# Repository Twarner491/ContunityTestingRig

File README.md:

### Devoloped by [Drew Griggs](http://fabacademy.org/2021/labs/charlotte/students/drew-griggs/about/) and [Teddy Warner](https://teddywarner.org/About-Me/about/).

## Documentation -

Our project idea, as discussed with RhythmLink, is a continuity testing rig. This project will be capable of testing and displaying the results of the pinout connections between two ends of a cable with different headers. Our goal is to create a continuity testing rig capable of testing and displaying the connections between the ends of two different cable headers. We will display the results to a webpage using the Raspberry Pico W microcontroller.

The concept behind this project is simple, but our method of display, as well as some methods to reduce the GPIO pins required for the microcontroller will be quite complex, so we worry that we might run into some issues here. The most challenging part of this project will likely be getting the web server to run correctly, as we will be using a RPI Pico W to host the server, but there are very few examples of a project such as this compared to something like an Arduino. A successful project would be able to test the continuity in real time and refresh the users web browser through a visually appealing display.

We used a few sources as guides to setting up a RPI web server, mainly Tom’s Hardware and the Raspberry Pi website - see the *sources* section below.

Our project is significantly more complex than these simple web servers, however, as we will refresh the page automatically, include some javascript and more complex HTML elements to improve the aesthetic, not to mention the continuity testing aspects.

Through the development of the project, we learned a great deal about the principles of static site design, multimedia design with 3D printing, and the integration of software and hardware components. As we developed the initial design stages of the project, we reminded ourselves of the horrors of debugging, going through countless coexisting issues that were causing the failure of our project. As we built up our initial prototype, we discovered, and ultimately resolved, issues involving our diode array, web server generation, board design, and many more. Similarly to our Fab Academy projects, we had many parts working in conjunction with each other. As we traversed the design and manufacturing process, we once again were reminded of the difficulty of getting each component of the project successfully integrated. At times, we would wonder from which component of the project our errors arose from.

Some of the major issues we encountered were due to errors in the board design. Due to an oversight in the main board, we did not include diodes for the final point of connection between each diode chain and output pin, which caused issues with reading pins that should not be high. Furthermore, we had an issue with our self test function. We initially decided to implement transistors to toggle and check each output and input pin, but due to voltage jumping between Gate and Drain despite no Source voltage, this part was unsuccessful. As such, we will not be making any further changes to the prototype, other than implementing a basic self test function with a predetermined cable.

### Electronic Design

The testing rig will likely consist of two separate boards, one main logic and interpretation board and one header board. The logic board will include a RPi Pico W to host the server and interpret data, a power regulation module, a diode array to reduce specific pins into their binary values (to conserve GPIO pins), and a large 2x20 pin header. The header board will include the connectors for each end of the cable and the 2x20 pin connector, as well as a possible self test function to ensure the functionality of the rig. The self test will include a jump between specific pins on each module, and an LED that will flash green assuming the test passes.

We used a few methods to allow the project to be operable on the Raspberry Pico. We designed and implemented an array of diodes to convert any individual input into a binary representation of its pin value, allowing us to test and read 15 possible different wires through 4 input pins. For the header connector board, we designed custom eagle footprints and libraries for the two types of connectors, as well as adding self-test circuits that will connect pins through the switch of a transistor.

Our project went somewhat to plan. Due to some issues in the testing of our board due to the precision of our lab’s PCB mills as well as the complexity of our board, we had some issues testing the main board. We eventually fixed a bug in the diode array, and the main board was working. The header board took less time, as it was less complex, but due to some issues with voltages jumping across transistors despite no source voltage, we were unable to include our initially planned self test function. After discussions with Rhythmlink, however, we determined that this would not be an issue, and since the board worked without the transistors soldered, we continued with testing. Web and software design and testing took the majority of our allocated time, as this was the first project of this type for both of us, so it took some getting used to programming a web server through micropython.

We mostly used tools oriented to PCB design in our project. We spent the majority of our machine use on the Bantam PCB mills, with some 3D printing of our enclosure towards the end of our project. Our files were EagleCad .sch and .brd schematic and boards, python files, fusion project files, and html files.

### Software

The operation of the Pico makes designing and editing a webpage in real time very annoying. It requires a string object to be sent through a library in the Pico, so we had to code a way to implement the updates of the test through splicing strings together. Apart from some hiccups in the testing of this component, however, the code was fairly simple. It loops through each of nine output pins, and reads the corresponding binary value of the input pins that corresponds to the pin number in the header cable.

### CAD

### Testing

https://github.com/user-attachments/assets/56f717f2-6f56-4a5b-b8bf-3c429beb7c11

https://github.com/user-attachments/assets/bd0a2b19-7a08-46a7-8804-3f2991451b49

### Assembly Instructions

- Download necessary files from github (link above)
- 3D print outer case
- Order or manufacture main and header board
- Solder components to each board
- Download Thonny and the python script
- Use dupont connectors and solid wires to create header cable adapters
- Add your wifi information to the ssid and password in the python file
- Boot the pico w with the boot file. Instructions can be found on raspberry pico article
- Run the script

## Sources -
 - [https://www.tomshardware.com/how-to/raspberry-pi-pico-setup](https://www.tomshardware.com/how-to/raspberry-pi-pico-setup)
 - [https://datasheets.raspberrypi.com/picow/pico-w-datasheet.pdf](https://datasheets.raspberrypi.com/picow/pico-w-datasheet.pdf)

---
- [Fork this repository](https://github.com/Twarner491/ContunityTestingRig/fork)
- [Watch this repo](https://github.com/Twarner491/ContunityTestingRig/subscription)
- [Create issue](https://github.com/Twarner491/ContunityTestingRig/issues/new)

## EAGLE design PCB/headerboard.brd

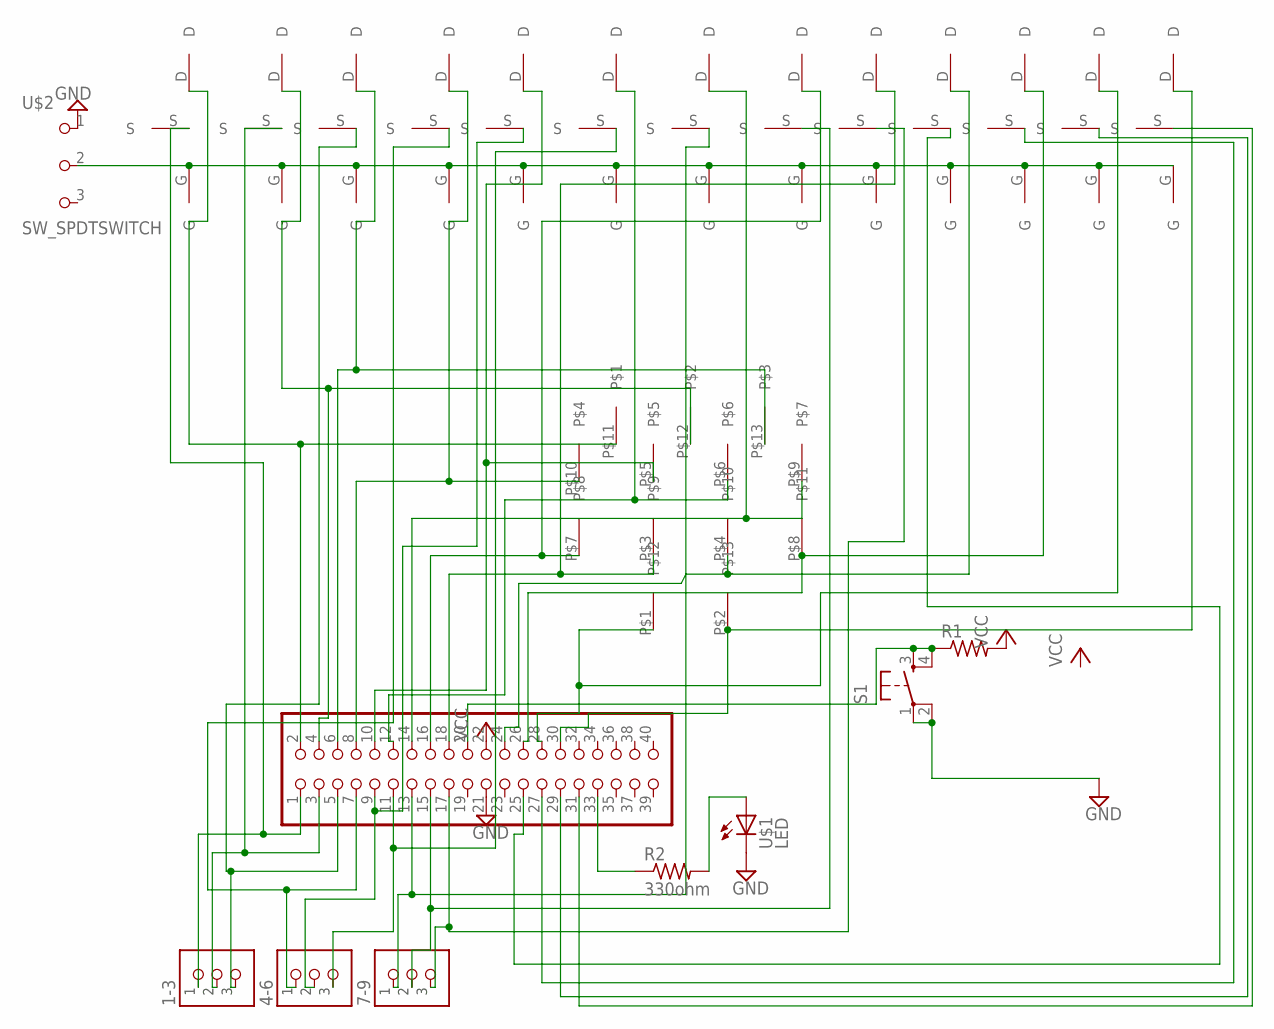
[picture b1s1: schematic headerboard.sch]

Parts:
1-3, 4-6, 7-9: CONN_03_TERM'-FABLAB'; ED555DS-3DS
JP1: PINHD-2X20; 2X20
R1: R1206FAB
R2: 330ohm; R1206FAB
S1: SW_SWITCH_TACTILE_6MM6MM_SWITCH; 6MM_SWITCH
U$1: LED; LED1206
U$2: SW_SPDTSWITCH; SPDTSWITCH
U$3, U$4, U$5, U$6, U$7, U$8, U$9, U$10, U$11, U$12, U$13, U$14, U$15: SOT23NMOS
U$19: 13PINHEADER; 13HEADER

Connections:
GND: JP1.21, S1.1, S1.2 (P1), U$1.2 (C), U$2.1
unnamed: U$2.2, U$3.G, U$4.G, U$5.G, U$6.G, U$7.G, U$8.G, U$9.G, U$10.G, U$11.G, U$12.G, U$13.G, U$14.G, U$15.G
unnamed: JP1.2, U$3.D, U$19.P$11
unnamed: JP1.4, U$4.D, U$19.P$12
unnamed: JP1.6, U$5.D, U$19.P$13
unnamed: JP1.8, U$6.D, U$19.P$10
unnamed: JP1.12, U$8.D, U$19.P$6
unnamed: JP1.26, U$13.D, U$19.P$8
unnamed: JP1.14, U$9.D, U$19.P$9
unnamed: JP1.16, U$10.D, U$19.P$7
unnamed: JP1.18, U$11.D, U$19.P$3
unnamed: 1-3.2, JP1.3, U$4.S
unnamed: JP1.28, U$14.D, U$19.P$1
unnamed: JP1.24, U$12.D, U$19.P$4
unnamed: JP1.30, U$15.D, U$19.P$2
unnamed: 1-3.3, JP1.5, U$5.S
unnamed: JP1.20, R1.1, S1.3 (S), S1.4 (S1)
unnamed: 4-6.1, JP1.7, U$6.S
unnamed: 4-6.2, JP1.9, U$7.S
unnamed: 4-6.3, JP1.11, U$8.S
unnamed: 7-9.1, JP1.13, U$9.S
unnamed: JP1.10, U$7.D, U$19.P$5
unnamed: 7-9.2, JP1.15, U$10.S
unnamed: 7-9.3, JP1.17, U$11.S
unnamed: JP1.25, U$12.S
unnamed: JP1.27, U$13.S
unnamed: JP1.29, U$14.S
unnamed: JP1.31, U$15.S
unnamed: JP1.33, R2.1
unnamed: R2.2, U$1.1 (A)
unnamed: 1-3.1, JP1.1, U$3.S
VCC: JP1.22, R1.2

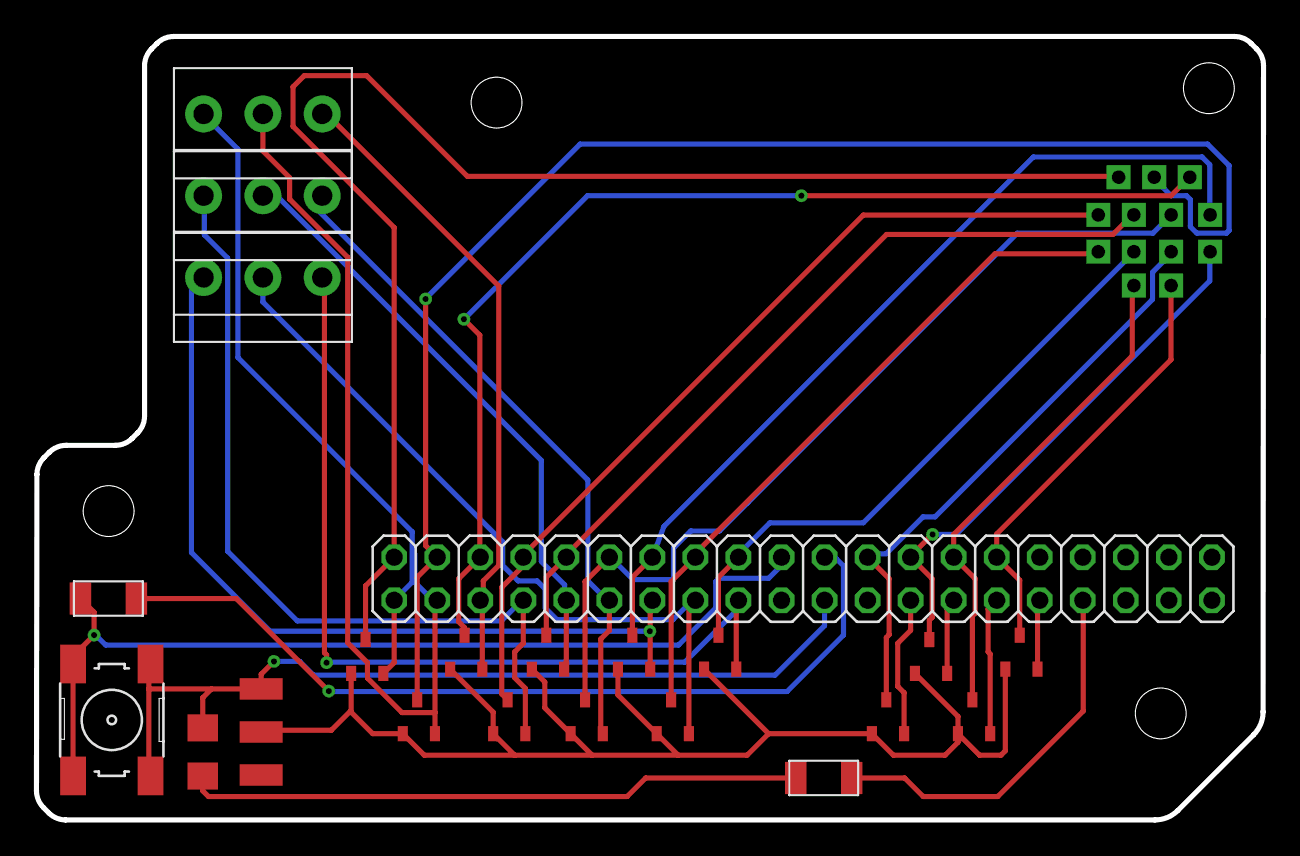
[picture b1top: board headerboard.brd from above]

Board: 2 copper layers, 72.4 x 46.2 mm, 23 parts (0 on the bottom side), 32 nets.

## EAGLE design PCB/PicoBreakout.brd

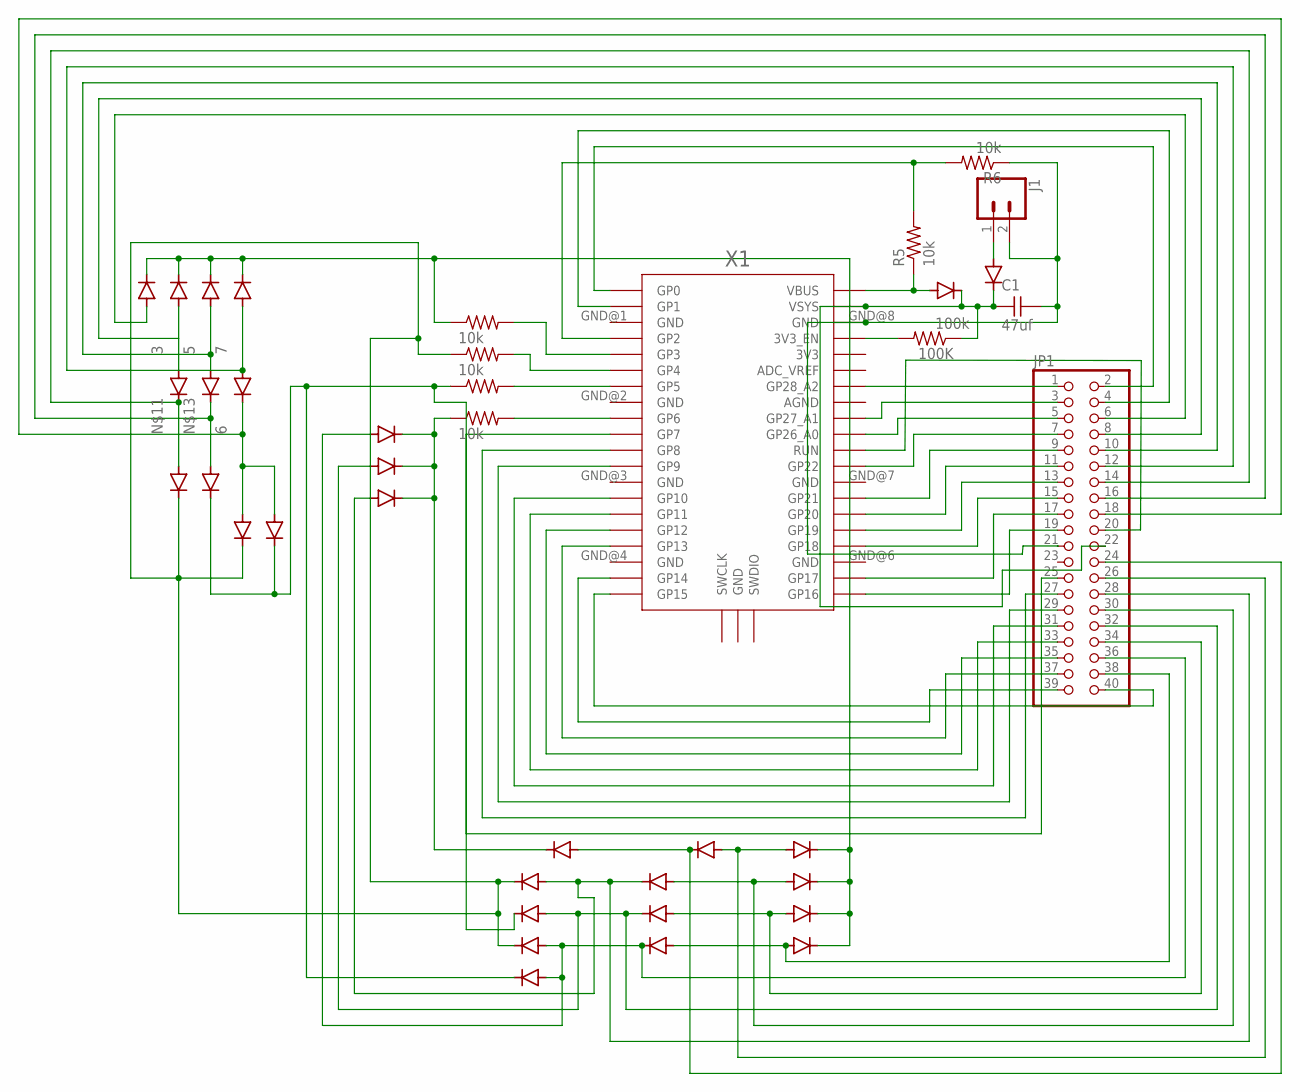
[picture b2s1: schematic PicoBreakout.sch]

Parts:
100K: 100k; R1206FAB
C1: 47uf; C1206FAB
D1, D2, D3, D4, D5, D6, D7, D8, D9, D10, D11, D12, D13, D14, D15, D16, D17, D18, D19, D20, D21, D22, D23, D24, D25, D26, D27, D28, D29: SCHOTTKY; MINI-SMA
J1: CONN_02LOCK_LONGPADS; 1X02_LOCK_LONGPADS
JP1: PINHD-2X20; 2X20
R1, R2, R3, R4, R5, R6: 10k; R1206FAB
X1: RPI_PICO_IG-TH; RPI_PICO_TH

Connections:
1: D1.KATHODE, D2.KATHODE, D3.KATHODE, D13.KATHODE, D14.KATHODE, D15.KATHODE, D16.KATHODE, D24.KATHODE, R1.1
3: D1.ANODE, D4.ANODE, JP1.8
4: D7.KATHODE, D17.KATHODE, D18.KATHODE, D25.KATHODE, R2.1
5: D2.ANODE, D5.ANODE, JP1.10
6: D6.KATHODE, D7.ANODE, D8.ANODE, JP1.18
7: D3.ANODE, D6.ANODE, JP1.12
8: D21.KATHODE, D22.KATHODE, D23.KATHODE, D26.KATHODE, R4.1
9: D9.ANODE, D13.ANODE, JP1.26
10: D10.KATHODE, D17.ANODE, D23.ANODE, JP1.28
11: D10.ANODE, D14.ANODE, JP1.30
12: D11.KATHODE, D19.ANODE, D22.ANODE, JP1.32
13: D11.ANODE, D15.ANODE, JP1.34
14: D12.KATHODE, D18.ANODE, D20.ANODE, D21.ANODE, JP1.36
15: D12.ANODE, D16.ANODE, JP1.38
unnamed: R1.2, X1.GP3
unnamed: R2.2, X1.GP4
unnamed: R3.2, X1.GP5
unnamed: R4.2, X1.GP6
unnamed: D8.KATHODE, D19.KATHODE, D20.KATHODE, D27.KATHODE, R3.1
unnamed: D24.ANODE, JP1.6
unnamed: D4.KATHODE, D25.ANODE, JP1.14
unnamed: D9.KATHODE, D26.ANODE, JP1.24
unnamed: D5.KATHODE, D27.ANODE, JP1.16
unnamed: D28.ANODE, J1.1
unnamed: C1.2, J1.2, JP1.21, R6.1, X1.GND@8 (GND)
unnamed: 100K.1, C1.1, D28.KATHODE, D29.KATHODE, JP1.22, X1.VSYS
unnamed: R5.2, R6.2, X1.GP2
unnamed: JP1.1, X1.GP28_A2
unnamed: 100K.2, X1.3V3_EN
unnamed: JP1.3, X1.GP27_A1
unnamed: JP1.5, X1.GP26_A0
unnamed: JP1.7, X1.GP22
unnamed: JP1.9, X1.GP21
unnamed: JP1.11, X1.GP20
unnamed: JP1.13, X1.GP19
unnamed: JP1.15, X1.GP18
unnamed: JP1.17, X1.GP17
unnamed: JP1.19, X1.GP16
unnamed: JP1.40, X1.GP15
unnamed: JP1.39, X1.GP14
unnamed: JP1.35, X1.GP12
unnamed: JP1.33, X1.GP11
unnamed: JP1.31, X1.GP10
unnamed: JP1.29, X1.GP9
unnamed: JP1.27, X1.GP8
unnamed: JP1.25, X1.GP7
unnamed: JP1.2, X1.GP0
unnamed: JP1.4, X1.GP1
unnamed: JP1.37, X1.GP13
unnamed: JP1.20, X1.RUN
unnamed: D29.ANODE, R5.1, X1.VBUS

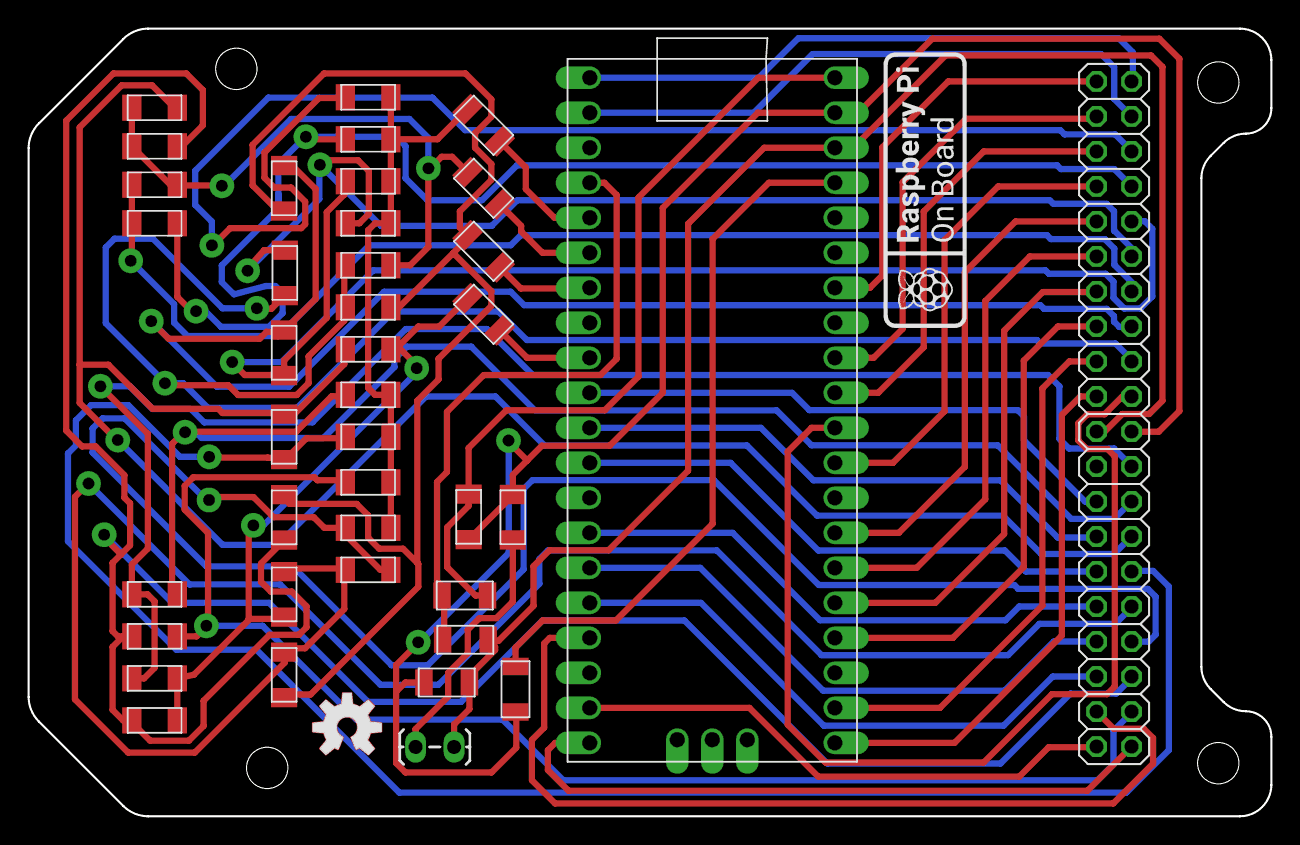
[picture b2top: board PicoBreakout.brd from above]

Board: 2 copper layers, 90.2 x 57.1 mm, 43 parts (0 on the bottom side), 51 nets.

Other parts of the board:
U$2: OSHW-LOGO-M_COPPER
U$3: RASPI_ON_BOARD_LOGO_20MM
U$4: OSHW-LOGO-M

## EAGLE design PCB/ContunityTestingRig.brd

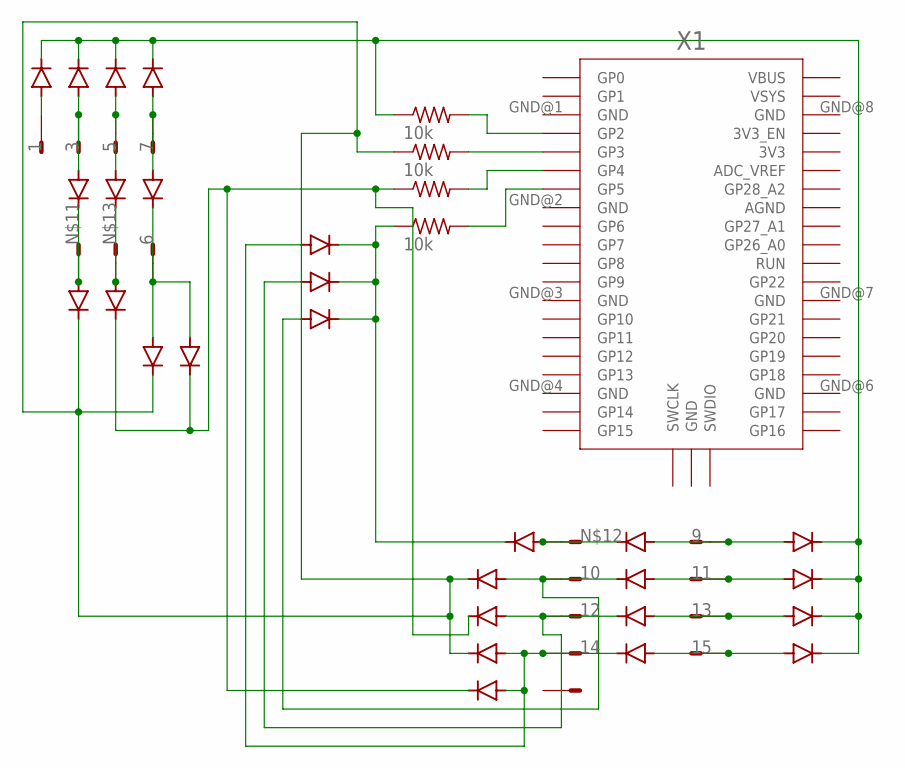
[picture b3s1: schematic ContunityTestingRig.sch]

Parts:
D1, D2, D3, D4, D5, D6, D7, D8, D9, D10, D11, D12, D13, D14, D15, D16, D17, D18, D19, D20, D21, D22, D23, D24, D25, D26, D27: SCHOTTKY; MINI-SMA
R1, R2, R3, R4: 10k; R1206FAB
SV1: 16E; 16P
X1: RPI_PICO_IG-SMD; RPI_PICO

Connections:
1: D1.KATHODE, D2.KATHODE, D3.KATHODE, D13.KATHODE, D14.KATHODE, D15.KATHODE, D16.KATHODE, D24.KATHODE, R1.1
3: D1.ANODE, D4.ANODE, SV1.3
4: D7.KATHODE, D17.KATHODE, D18.KATHODE, D25.KATHODE, R2.1
5: D2.ANODE, D5.ANODE, SV1.5
6: D6.KATHODE, D7.ANODE, D8.ANODE, SV1.6
7: D3.ANODE, D6.ANODE, SV1.7
8: D21.KATHODE, D22.KATHODE, D23.KATHODE, D26.KATHODE, R4.1
9: D9.ANODE, D13.ANODE, SV1.9
10: D10.KATHODE, D17.ANODE, D23.ANODE, SV1.10
11: D10.ANODE, D14.ANODE, SV1.11
12: D11.KATHODE, D19.ANODE, D22.ANODE, SV1.12
13: D11.ANODE, D15.ANODE, SV1.13
14: D12.KATHODE, D18.ANODE, D20.ANODE, D21.ANODE, SV1.14
15: D12.ANODE, D16.ANODE, SV1.15
unnamed: R1.2, X1.GP2
unnamed: R2.2, X1.GP3
unnamed: R3.2, X1.GP4
unnamed: R4.2, X1.GP5
unnamed: D8.KATHODE, D19.KATHODE, D20.KATHODE, D27.KATHODE, R3.1
unnamed: D24.ANODE, SV1.1
unnamed: D4.KATHODE, D25.ANODE, SV1.2
unnamed: D9.KATHODE, D26.ANODE, SV1.8
unnamed: D5.KATHODE, D27.ANODE, SV1.4

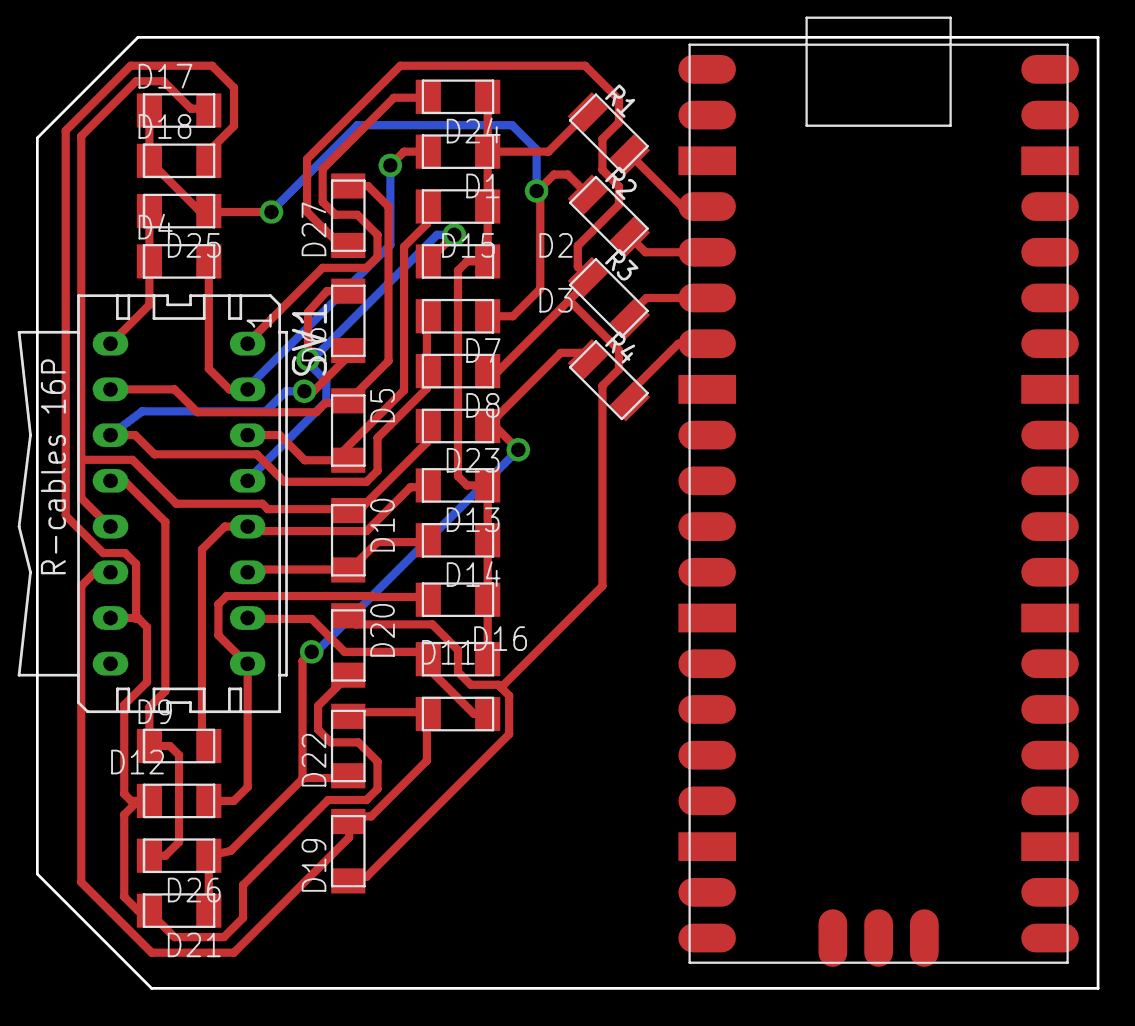
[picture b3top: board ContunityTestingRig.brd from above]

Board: 2 copper layers, 58.9 x 52.8 mm, 33 parts (0 on the bottom side), 23 nets.

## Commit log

2022-10-08 inital push
2022-10-08 README Fix
2022-10-21 Souce Addation
2022-10-21 Trace Fix
2022-10-22 ReadMe Update
2022-11-10 Create SiteCode
2022-11-10 Update SiteCode
2022-11-28 11/28/2022
2022-11-28 ContTest Fix
2022-11-29 Advanced topics in engineering
    13 Pin header svg object to be displayed in website
2022-12-07 schematic push
2023-01-05 PCB Updates
2023-01-06 .b file remove
2023-01-09 PCB v2
2023-01-10 PCB push
2023-01-31 updated run trace
2023-01-31 added header board schematic
2023-02-09 updated pico board
2023-02-13 header board and schematic
2023-02-15 brd updates
2023-03-09 Final Code Updates
2023-03-23 3MF Updates
2023-03-28 Media push
2023-03-28 Embed push
2023-03-28 test
2023-03-28 electric bogaloo
2023-03-28 video push
2023-03-28 update spelling
2023-04-27 Readme updates

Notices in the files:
parts and their libraries:
SparkFun-Connectors: Licensing: Creative Commons ShareAlike 4.0 International - https://creativecommons.org/licenses/by-sa/4.0
